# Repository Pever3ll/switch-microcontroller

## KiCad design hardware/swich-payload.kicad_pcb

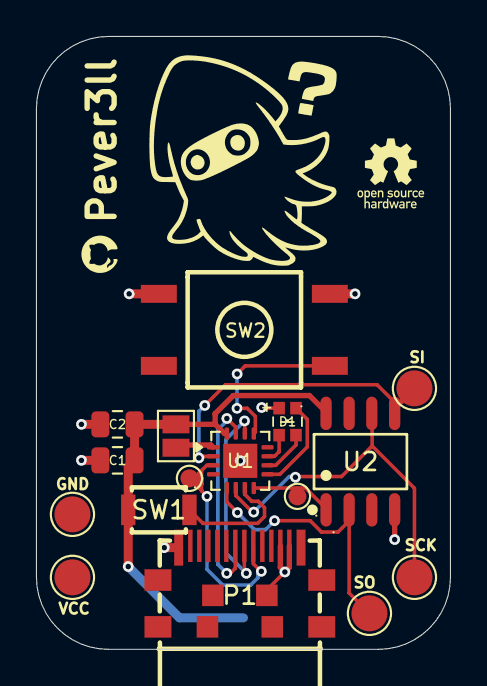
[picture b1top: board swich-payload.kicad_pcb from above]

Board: 2 copper layers, 23.0 x 34.0 mm, 17 parts (1 on the bottom side), 15 nets.

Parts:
BT1: Battery_Cell; BAT-SMD_BHSD-2032-SM
C1: 0.1 uF; C_0805_2012Metric
C2: 10 uF; C_0805_2012Metric
D1: GL-1615RGB01-B; LED-SMD_4P-L1.6-W1.5-BL-C9900013097
JP1: SolderJumper_2_Open; SolderJumper-2_P1.3mm_Open_Pad1.0x1.5mm
P1: USB_C_Plug_USB2.0; USB-C-SMD_TYPE-C-31-G-10
SW1: SW_Push; SW-SMD_L3.0-W2.5-P3.40-LS4.0-EH
SW2: TS6635PA 250GF TACTILE SWITCH; SW-SMD_4P-L6.4-W6.3-P4.00-LS9.5
TP1, TP2, TP6, TP7, TP8: TestPoint_Square; TestPoint_Pad_D2.0mm
TP3, TP5: TestPoint_Square; TestPoint_Pad_D1.0mm
U1: CH554P; QFN-16-1EP_3x3mm_P0.5mm_EP1.9x1.9mm
U2: ZD25WD20CTIGT; SOP-8_L4.9-W3.9-P1.27-LS6.0-BL

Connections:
/BUTTON: SW2.1, U1.13 (P3.4/PWM2/RXD1_/T0)
/CS: TP5.1 (1_1), U1.8 (P1.0/T2/CAP1/TIN0), U2.1 (~CS)
/RBG R: D1.1, U1.9 (P3.1/PWM2_/TXD)
/RGB B: D1.3, U1.11 (P1.1/T2EX/CAP2/TIN1/AIN0)
/RGB G: D1.4, U1.10 (P3.0/PWM1_/RXD)
/RST: SW1.1, U1.7 (RST/T2EX_/CAP2_)
/SCK: TP6.1 (1_1), U1.6 (P1.7/SCK/TXD1/TIN5), U2.6 (SCLK)
/SI: TP8.1 (1_1), U1.2 (P1.5/MOSI/PWM1/TIN3/AIN2), U2.5 (SI/IO0)
/SO: TP7.1 (1_1), U1.5 (P1.6/MISO/RXD1/TIN4), U2.2 (SO/IO1)
/USB CC: P1.A5 (CC), TP3.1 (1_1), U1.3 (P1.4/T2_/CAP1_/SCS/TIN2/AIN1)
/USB D+: P1.A6 (D+), U1.14 (P3.6/UDP)
/USB D-: P1.A7 (D-), U1.15 (P3.7/UDM)
GND: BT1.2 (-), C1.2, C2.2, D1.2, P1.A1 (GND), P1.B1 (GND), P1.B12 (GND), SW2.3, SW2.4, TP2.1 (1_1), U1.17 (GND/VSS), U2.4 (VSS)
unnamed: JP1.2 (B), U1.1 (V33)
VCC: BT1.1 (+), C1.1, C2.1, JP1.1 (A), SW1.2, TP1.1 (1_1), U1.16 (VCC/VDD), U2.8 (VCC)
